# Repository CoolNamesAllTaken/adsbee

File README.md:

# ADSBee

ADSBee is a family of open-source, dual-band ADS-B receivers from [Pants for Birds LLC](https://pantsforbirds.com). Every ADSBee decodes 1090 MHz Mode S / ADS-B and 978 MHz UAT transmissions onboard — no SDR dongle, FPGA, or host computer required — maintains an aircraft dictionary, and streams tracked aircraft over UART (and, on the 1090 family, WiFi / Ethernet) in a wide range of output protocols. This repository holds the firmware, hardware design files, datasheets, and host software for the whole family.

There are two product lines, which share most of their firmware (`firmware/common/`):

| | **ADSBee 1090** | **ADSBee 1421** |
|---|---|---|
| Best for | Ground stations, feeders, networked receivers | Ultra-low-power embedded / UAS detect-and-avoid |
| Processors | RP2040 + ESP32-S3 + CC1312 | TI CC1314R10 + Semtech LR2021 |
| 1090 MHz | Custom RF frontend + RP2040 PIO decoder | LR2021 OOK receiver |
| 978 MHz UAT | CC1312 sub-GHz radio | CC1314 sub-GHz radio (uplink reception selectable) |
| Interfaces | USB, UART, WiFi, Ethernet (PoE pant / W5500), GNSS | UART (AT commands), SYNC line, LR2021 SPI passthrough |
| Power | ~1W | ~19 mA at 1.8–3.3 V |
| Firmware | [`firmware/adsbee_1090/`](firmware/adsbee_1090/) | [`firmware/adsbee_1421/`](firmware/adsbee_1421/) |

## Safety Notice

We work hard to make ADSBee products performant and reliable, but not all aircraft broadcast their location, messages can be lost or corrupted, and hardware or software can fail. ADSBee cannot guarantee detection or accurate reporting of all traffic. Users are responsible for evaluating its suitability for their application and for the safe operation of any system it is integrated into. See our [terms of sale](https://pantsforbirds.com/terms-of-sale/#warranty) and [license](LICENSE) for full terms.

## Products and Where to Buy

All ADSBee devices are designed and sold by Pants for Birds LLC. Purchasing a device is the best way to support the project. Product pages, datasheets, and the [Quick Start Guide](https://pantsforbirds.com/adsbee/quick-start/) live at [pantsforbirds.com](https://pantsforbirds.com/adsbee/).

### ADSBee 1090 family

| | |
|---|---|
|  | **[ADSBee 1090U](https://pantsforbirds.com/product/adsbee-1090u/)** — RP2040, ESP32-S3, CC1312, and a custom 1090 MHz RF frontend on a single PCBA, enabling all multi-band receive and networking functions (Ethernet requires an external pant). [Datasheet](word/exports/datasheet_adsbee_1090.pdf) |
|  | **[ADSBee m1090](https://pantsforbirds.com/product/adsbee-m1090/)** — solder-down module containing only the 1090 MHz frontend and RP2040. Add a CC1312 and ESP32 on your carrier board for the full 1090U feature set, running the same firmware image. Drops one of the 1090U's two LNA stages for lower power and better ultra-close-range performance; populate an external LNA on the carrier for equivalent maximum range. An [m1090 Eval Board](https://pantsforbirds.com/product/adsbee-m1090-eval-board/) is available ([datasheet](word/exports/datasheet_adsbee_m1090_eval_board.pdf)). |
|  | **[GS3M PoE](https://pantsforbirds.com/product/adsbee-gs3m-poe/)** — the ADSBee 1090U in a ruggedized, weatherproof enclosure, connected and powered over 802.3af Power over Ethernet for industrial and outdoor installations. [Datasheet](word/exports/datasheet_gs3m_poe.pdf) |

### ADSBee 1421 family

| | |
|---|---|
|  | **[ADSBee m1421](https://pantsforbirds.com/product/adsbee-m1421/)** — high-performance, ultra-low-power dual-band receiver module (TI CC1314R10 + Semtech LR2021). Receives 1090 MHz Mode S and 978 MHz UAT, tracks up to 400 aircraft onboard, and reports over UART. Weighs 1.85 g. [Datasheet](word/exports/datasheet_adsbee_m1421.pdf) |
|  | **[ADSBee 1421 Developer Kit](https://pantsforbirds.com/product/adsbee-1421-devkit/)** — compact carrier board for the m1421 with a power combiner so a single lightweight dual-band antenna feeds both the 1090 MHz and 978 MHz inputs. Includes the PCBA with ARM-JTAG header, wire harness, USB programmer, and a dual-band ADS-B antenna. [Datasheet](word/exports/datasheet_adsbee_1421_devkit.pdf) |

## ADSBee 1090

ADSBee 1090 is an open-source multi-band radio receiver and decoder for ADS-B packets transmitted by aircraft and ground stations. It is based on an RP2040 microcontroller and utilizes two independent PIO blocks to find and decode ADS-B messages without the need for an FPGA. ADSBee 1090 includes a radio receiver frontend with filtering and amplification, as well as a software-defined comparator circuit with an adjustable trigger threshold for customizable receive sensitivity in a diverse range of RF environments.

### Features
* Decoding of 1090 MHz transponder signals (ADS-B and Mode S).
* Decoding of 978 MHz UAT transponder signals (ADS-B) and uplink data (FIS-B/TIS-B).
* 1x USB console input / output for changing parameters and transmitting data.
* 1x UART for reporting data or ingesting GNSS information.
* Built-in EEPROM for storing nonvolatile settings.
* Feature-rich AT command set for customizing baud rates, output data protocols, signal conditioning values, etc.
* Multiple supported output protocols:
    * Raw packets
    * MAVLINK1
    * MAVLINK2
    * GDL90
    * Mode S Beast
    * Aircraft JSON
    * CSBee (custom information-rich ASCII protocol)
* 2.4 GHz 802.11 radio for automatic streaming of decoded values to custom endpoints on the internet. No external compute required, just add WiFi and power!
* Ethernet interface (requires external PoE pant or W5500 IC).
* GNSS module connector for MLAT and ground station location information.
* ~1W power draw.

### Architecture
ADSBee 1090 utilizes some basic RF hardware (SAW filters, LNA, logarithmic power detector) to amplify the received pulse-position-modulated ADS-B waveform into a pulse train that is conditioned by a comparator and fed to a PIO input pin on the RP2040. The RP2040 utilizes two PIO state machines, one for preamble detection and one for Manchester decoding of the message body, to decode the ADS-B message. This offers significant cost and power savings over FPGA-based solutions that solve the same problem.

A filtered PWM output from the RP2040 can be used to adjust the bias of the data slicer comparator circuit on the output of the receive signal chain, allowing logarithmic adjustments in receiver sensitivity which can be used to filter out weaker ADS-B signals in congested environments or maximize sensitivity for increased receive range.

There are two devices connected to the RP2040 via a common SPI bus: a CC1312 for secondary band receive and an ESP32-S3 for networking functions.

The CC1312 can be tuned to a variety of sub-GHz frequencies to decode UAT messages (and potentially more protocols in the future). These messages are forwarded to the RP2040 over SPI and reported through a unified interface along with the Mode S packets received by the RP2040.

The ESP32-S3 ingests raw packets from the RP2040 and maintains its own aircraft dictionary for reporting over network interfaces (WiFi, Ethernet). The RP2040's dictionary holds 400 aircraft for its USB and UART outputs; the ESP32-S3's holds 200.

All three microcontrollers utilize code stored on the RP2040's external flash chip, so firmware updates are conducted by flashing a single firmware image to the RP2040, which in turn flashes updated firmware images to the CC1312 and ESP32-S3.

## ADSBee 1421

ADSBee 1421 is an ultra-low-power dual band ADS-B receiver, built around a TI CC1314R10 low-power RF MCU and a Semtech LR2021 radio. The LR2021 provides best-in-class sensitivity for the high-baud-rate OOK 1090 MHz Mode S waveform, while the CC1314's sub-GHz RF core receives 978 MHz UAT and its Cortex-M33 does all demodulation, FEC, decoding, and aircraft tracking. The whole receiver draws about 19 mA and weighs under 2 g, making it suited to UAS detect-and-avoid and other power- and weight-constrained applications.

### Features
* Decoding of 1090 MHz transponder signals (ADS-B and Mode S), with selectable preamble modes for range vs. message-type coverage (`AT+R1090_PREAMBLE`).
* Decoding of 978 MHz UAT transponder signals (ADS-B) and ground uplink data (FIS-B/TIS-B). Uplink reception can be disabled independently (`AT+SUBG_MODE=UAT_RX_NO_UPLINK`) to save airtime and CPU when only traffic is needed.
* Onboard aircraft dictionary for up to 400 simultaneous targets.
* UART console with a feature-rich AT command set (baud rate, output protocol, receiver position, gain, logging, …); settings persist in flash.
* Multiple supported output protocols: Raw packets, CSBee, MAVLINK1, MAVLINK2, GDL90, Mode S Beast, Aircraft JSON.
* SYNC line for host-controlled deep sleep (STANDBY with SRAM retained), which also hands the LR2021 SPI bus to an external MCU — e.g. to use the LR2021's 2.4 GHz radio for LoRa or mesh networking.
* Firmware updates over the UART ROM bootloader (no debugger needed) or JTAG. Holding SYNC high through a reset enters the bootloader, so any host that drives a USB-UART adapter's RTS → SYNC and DTR → RESET_N (or the included ADSBee 1421 Programmer) can reflash the module remotely. See [Reflashing over UART: the SYNC bootloader backdoor](firmware/adsbee_1421/README.md#reflashing-over-uart-the-sync-bootloader-backdoor).
* Ultra-low power: ~19 mA at 1.8–3.3 V.

### Architecture
The CC1314R10 runs a NoRTOS super-loop: it polls the LR2021 over SPI for 1090 MHz OOK frames, services its own RF core's UAT receptions (ADS-B and uplink are distinguished by sync word, so uplink can be switched off at the radio), runs the shared Mode S / UAT decoders and aircraft dictionary from `firmware/common/`, and reports over the console UART. A host can suspend the device by driving SYNC high; on wake the receiver re-initializes itself. SYNC is also the ROM bootloader backdoor pin, so a reset while SYNC is high enters the serial bootloader. See [`firmware/adsbee_1421/AGENTS.md`](firmware/adsbee_1421/AGENTS.md) for the build guide and the SYNC sleep / LR2021 bus-handoff contract, and the [m1421 datasheet](word/exports/datasheet_adsbee_m1421.pdf) for the full AT command reference.

## Repository Layout

| Path | Contents |
|---|---|
| [`firmware/`](firmware/) | All firmware. [`adsbee_1090/`](firmware/adsbee_1090/) (RP2040 `pico/`, `esp/`, CC1312 `ti/`), [`adsbee_1421/`](firmware/adsbee_1421/) (CC1314 `ti/`, RP2040-Zero `programmer/`, the ADSBee 1421 Programmer), [`common/`](firmware/common/) (shared decoders, aircraft dictionary, comms, settings), `modules/` (submodules: cppAT, googletest, …), [`scripts/`](firmware/scripts/) (dev tooling), [`build.sh`](firmware/build.sh) dispatcher. |
| [`software/`](software/) | Host software: [`adsbee_1421_console/`](software/adsbee_1421_console/) (single-file Web Serial console + UART flasher for the 1421), `adsbee/` (Python package), `serial_logger/`, and `tar1090/` / `ultrafeeder/` / `ultra2/` feeder compose files. |
| [`ci/`](ci/) | Hardware-in-the-loop USB/UF2 + OTA flash test run by the self-hosted CI runner. |
| [`kicad/`](kicad/) | Hardware design files (ADSBee 1090, 1090U, frontend prototypes, panels). |
| [`3d/`](3d/) | Enclosure exports and CAD links. |
| [`ltspice/`](ltspice/), [`excel/`](excel/) | RF / analog simulations and design calculations. |
| [`affinity/`](affinity/) | Diagrams and promotional artwork sources. |
| [`word/`](word/) | Product datasheets and firmware reference guide (`.docx` sources, PDFs in [`word/exports/`](word/exports/)). |
| [`references/`](references/) | Protocol specifications and component datasheets. |
| [`images/`](images/) | Images used by this README. |

## Building and Flashing Firmware

All toolchains live in Docker containers, so the only host requirements are Docker and git.

```bash
git clone https://github.com/CoolNamesAllTaken/adsbee.git
cd adsbee
bash firmware/scripts/setup_dev.sh        # init submodules + install the pre-commit version-check hook
bash firmware/build.sh adsbee_1090        # RP2040 + ESP32-S3 + CC1312 -> combined.uf2
bash firmware/build.sh adsbee_1421        # CC1314R10 -> adsbee_1421-<version>.hex
```

* **[`firmware/README.md`](firmware/README.md)** — prerequisites, the build dispatcher, build targets and outputs.
* **[`firmware/AGENTS.md`](firmware/AGENTS.md)** — firmware architecture overview and the version-management rules.
* **ADSBee 1090:** [`firmware/adsbee_1090/Developers_Guide.md`](firmware/adsbee_1090/Developers_Guide.md) covers the three-processor build order, flashing (`combined.uf2` over USB BOOTSEL, or OTA through the ESP32 web interface), and recovery.
* **ADSBee 1421:** [`firmware/adsbee_1421/AGENTS.md`](firmware/adsbee_1421/AGENTS.md) covers the build; flash over JTAG with a J-Link ([`firmware/adsbee_1421/ti/README.md`](firmware/adsbee_1421/ti/README.md)), or over UART using the ROM bootloader ([SYNC bootloader backdoor](firmware/adsbee_1421/README.md#reflashing-over-uart-the-sync-bootloader-backdoor)) via the [ADSBee 1421 Programmer](firmware/adsbee_1421/programmer/README.md) (an RP2040-Zero board included in the Developer Kit), a host script driving RTS/DTR, or the **Upload Firmware** button in the [web console](software/adsbee_1421_console/README.md).

Prebuilt firmware is published on the [Releases page](https://github.com/CoolNamesAllTaken/adsbee/releases). Releases are tagged per product as `adsbee_1090-<major>.<minor>.<patch>` and `adsbee_1421-<major>.<minor>.<patch>` (release candidates carry an `-rcN` suffix). `AT+DEVICE_INFO?` reports the firmware version running on a device.

## Support, Bugs, and Feature Requests

* **Getting started / using a device:** start with the [Quick Start Guide](https://pantsforbirds.com/adsbee/quick-start/) and the product datasheets in [`word/exports/`](word/exports/) (AT command reference, reporting protocols, pinouts).
* **Purchasing, orders, warranty, and hardware support:** contact Pants for Birds through [pantsforbirds.com/contact](https://pantsforbirds.com/contact/).
* **Firmware / software bugs:** open a [GitHub Issue](https://github.com/CoolNamesAllTaken/adsbee/issues). Please include:
  * which product (1090U, m1090, GS3M PoE, m1421, 1421 Developer Kit) and the output of `AT+DEVICE_INFO?` (part code and firmware version);
  * what you expected vs. what happened, and steps to reproduce;
  * relevant console output (`AT+LOG_LEVEL=INFO` makes the device chattier) and, for the 1090 family, the web interface/feed configuration involved.
* **Feature requests and questions:** also welcome as GitHub Issues; please tag the title with the product family.

## Contributing

Contributions are welcome (bug fixes, new output protocols, decoder improvements, documentation, etc)! Please follow the steps below to contribute a change.

1. Fork the repo and create a branch from `main`.
2. Run `bash firmware/scripts/setup_dev.sh` once. It initializes submodules and installs a git pre-commit hook that enforces the version rule below.
3. Make your change. Any change under `firmware/adsbee_1090/`, `firmware/adsbee_1421/`, or `firmware/common/` must ship under a firmware version that has not been released yet for the affected product(s) (`firmware/common/coprocessor/object_dictionary.cpp` for 1090, `firmware/adsbee_1421/ti/object_dictionary/object_dictionary.cpp` for 1421; a `common/` change concerns both). If main is already on the next unreleased RC, keep it; if its version matches a release tag, move to the next unreleased RC. Note that devices only reflash coprocessors on a version mismatch, so you will need to force a reflash or bump the software version to test your code [`firmware/AGENTS.md`](firmware/AGENTS.md). When have finished testing and go to you submit your PR, ensure that your firmware version matches the version string in main! Firmware versions are only rolled upon each release.
4. If you add or change an AT command, reporting protocol, or other user-visible behavior, update the corresponding datasheet in [`word/`](word/).
5. Build locally with `firmware/build.sh` and, for 1090 changes, run the host unit tests (`bash firmware/build.sh adsbee_1090 test`).
6. Open a pull request against `main`. [CI](https://github.com/CoolNamesAllTaken/adsbee/actions/workflows/firmware.yml) builds every target and runs the unit tests; the hardware-in-the-loop flash test runs on `main` after merge.

By contributing you agree that your contributions are licensed under the GPL-3.0.

## License

ADSBee firmware, software, and design files in this repository are released under the [GNU General Public License v3.0](LICENSE). ADSBee is a product of Pants for Birds LLC.

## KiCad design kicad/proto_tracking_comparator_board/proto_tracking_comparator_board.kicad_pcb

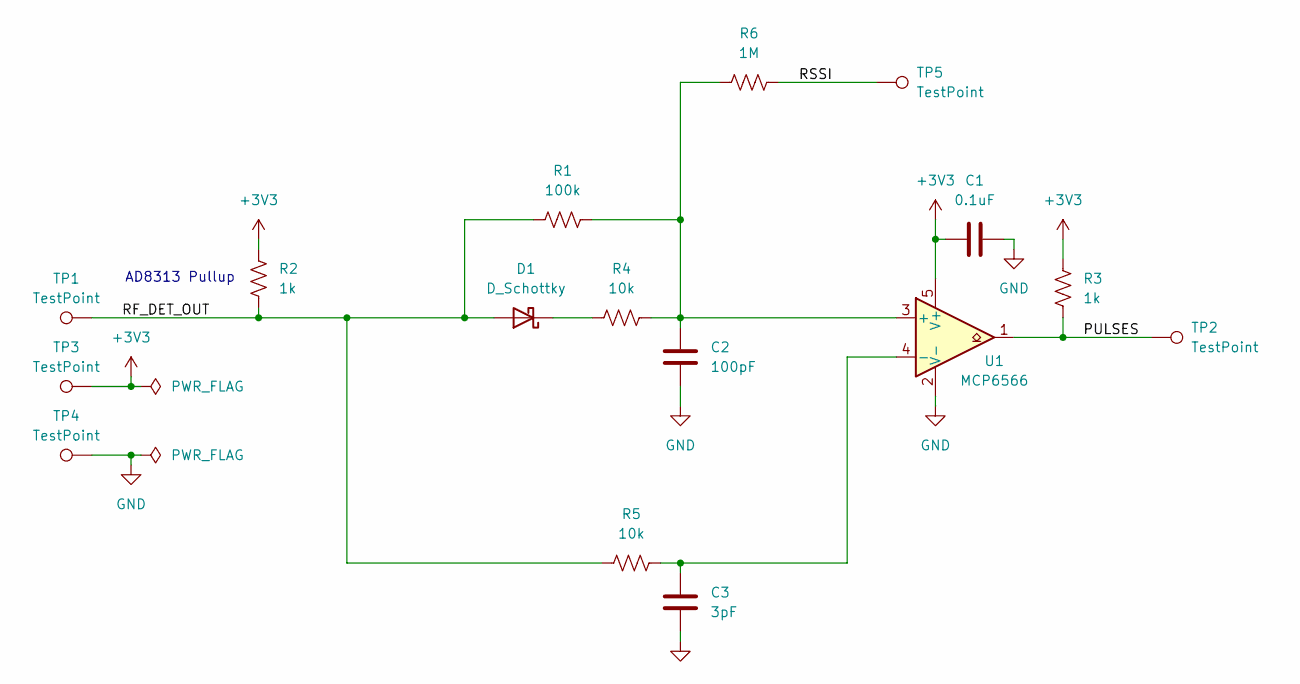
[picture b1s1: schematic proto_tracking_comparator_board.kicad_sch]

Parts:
C1: 0.1uF; C_0603_1608Metric
C2: 100pF; C_0603_1608Metric
C3: 3pF; C_0603_1608Metric
D1: D_Schottky; D_0402_1005Metric
R1: 100k; R_0603_1608Metric
R2, R3: 1k; R_0603_1608Metric
R4, R5: 10k; R_0603_1608Metric
R6: 1M; R_0603_1608Metric
TP1, TP2, TP3, TP4, TP5: TestPoint; TestPoint_Pad_1.0x1.0mm
U1: MCP6566; SOT-353_SC-70-5

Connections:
+3V3: C1.2, R2.1, R3.1, TP3.1, U1.5 (V+)
/PULSES: R3.2, TP2.1, U1.1
/RF_DET_OUT: D1.2 (A), R1.1, R2.2, R5.1, TP1.1
/RSSI: R6.2, TP5.1
GND: C1.1, C2.2, C3.2, TP4.1, U1.2 (V-)
unnamed: D1.1 (K), R4.1
unnamed: C2.1, R1.2, R4.2, R6.1, U1.3 (+)
unnamed: C3.1, R5.2, U1.4 (-)

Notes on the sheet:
AD8313 Pullup

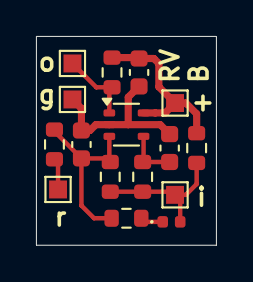
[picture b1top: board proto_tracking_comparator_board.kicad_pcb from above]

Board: 2 copper layers, 10.0 x 11.6 mm, 16 parts (0 on the bottom side), 8 nets.

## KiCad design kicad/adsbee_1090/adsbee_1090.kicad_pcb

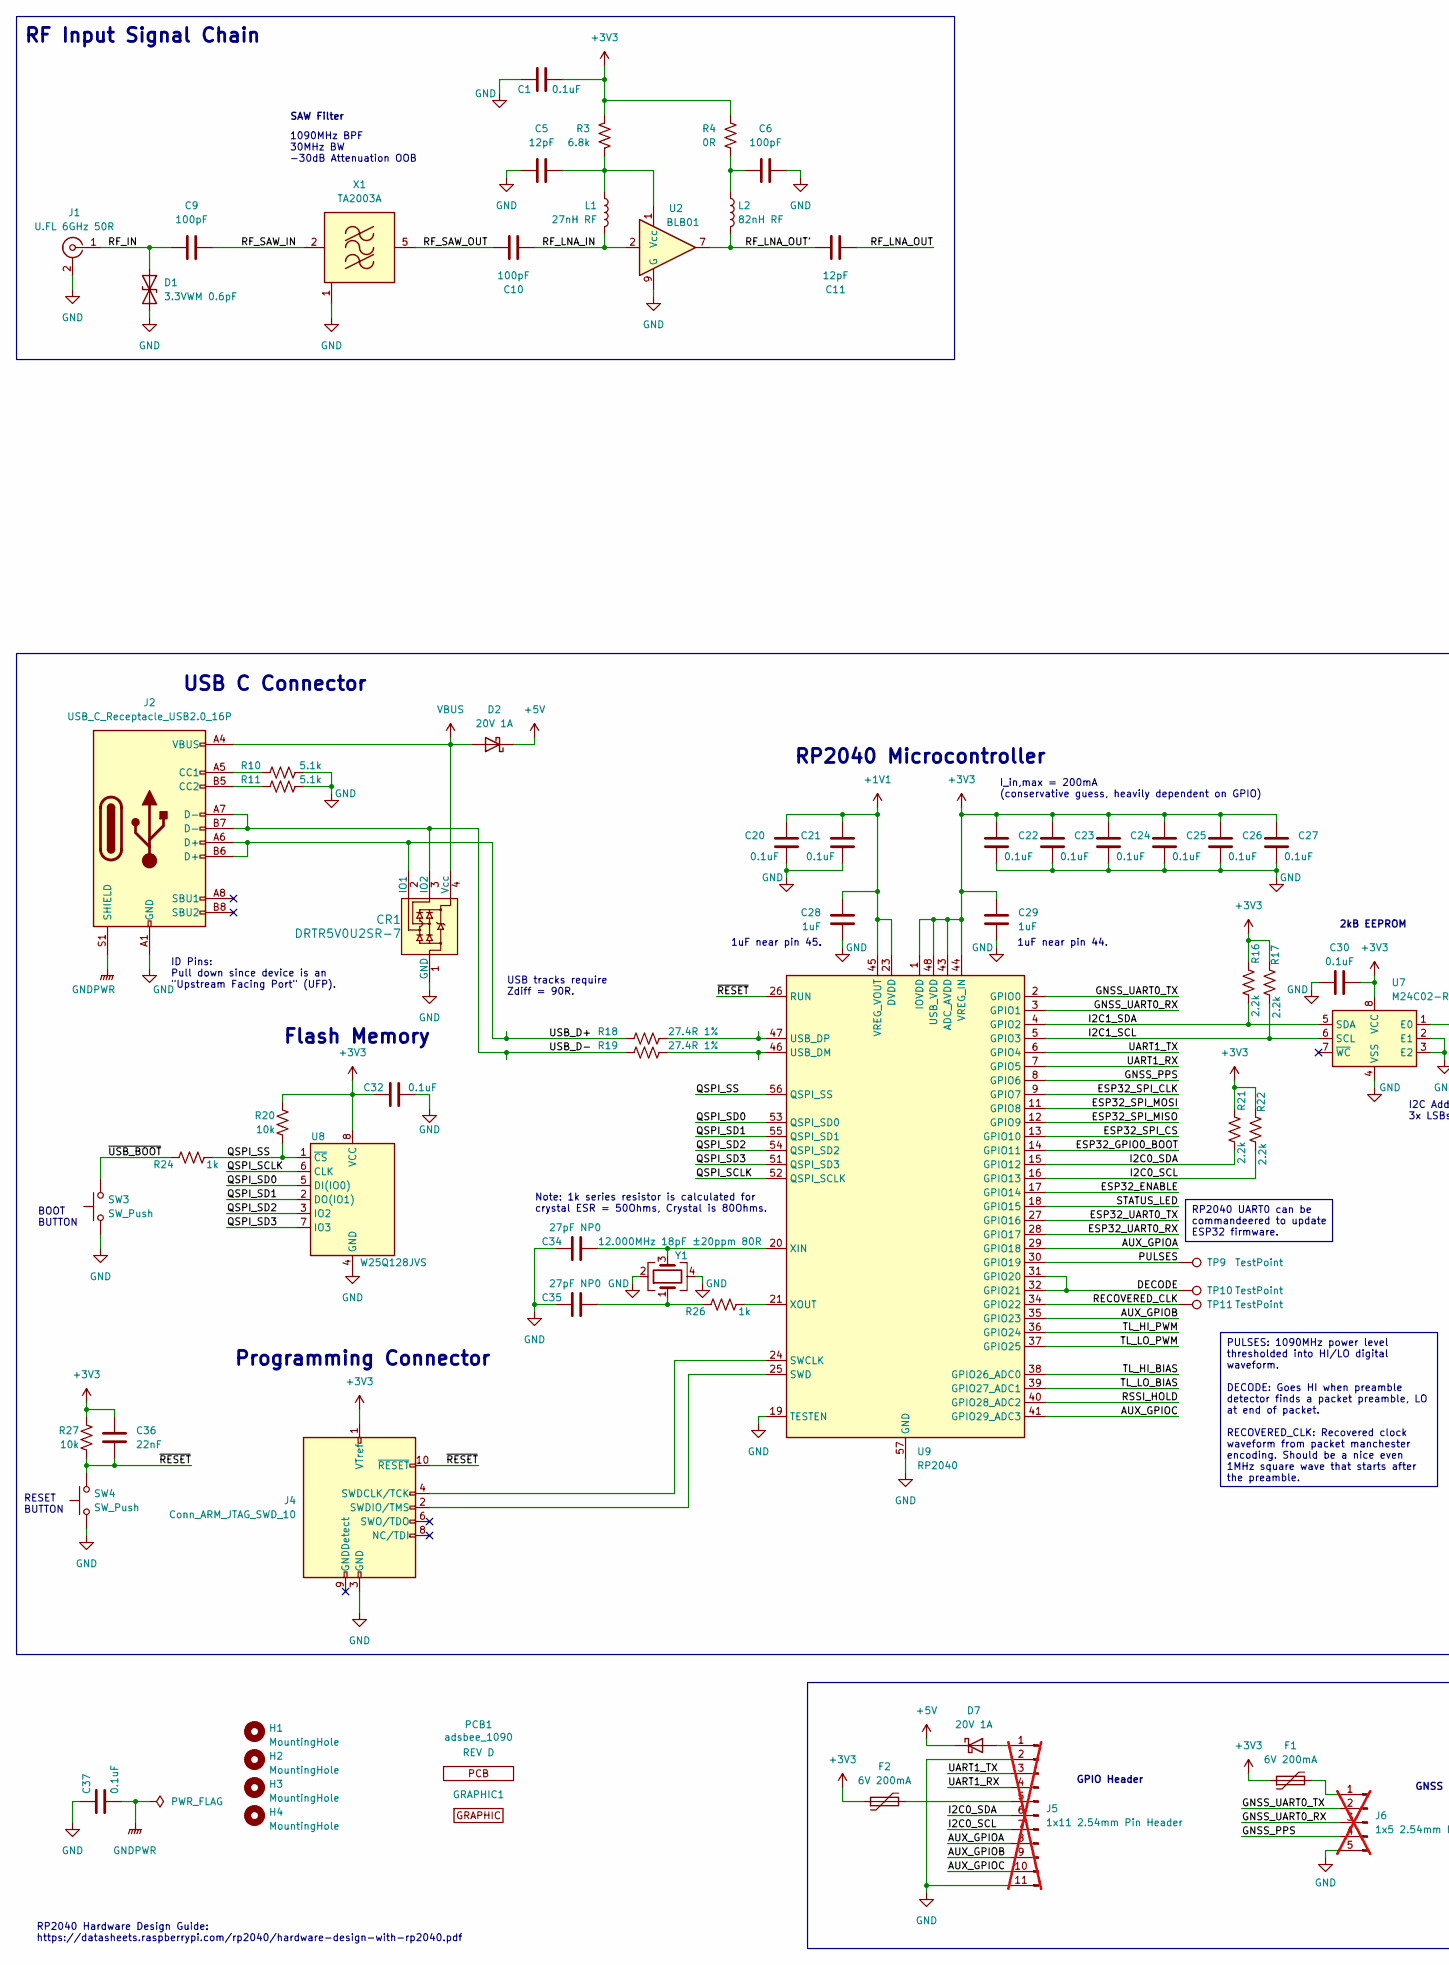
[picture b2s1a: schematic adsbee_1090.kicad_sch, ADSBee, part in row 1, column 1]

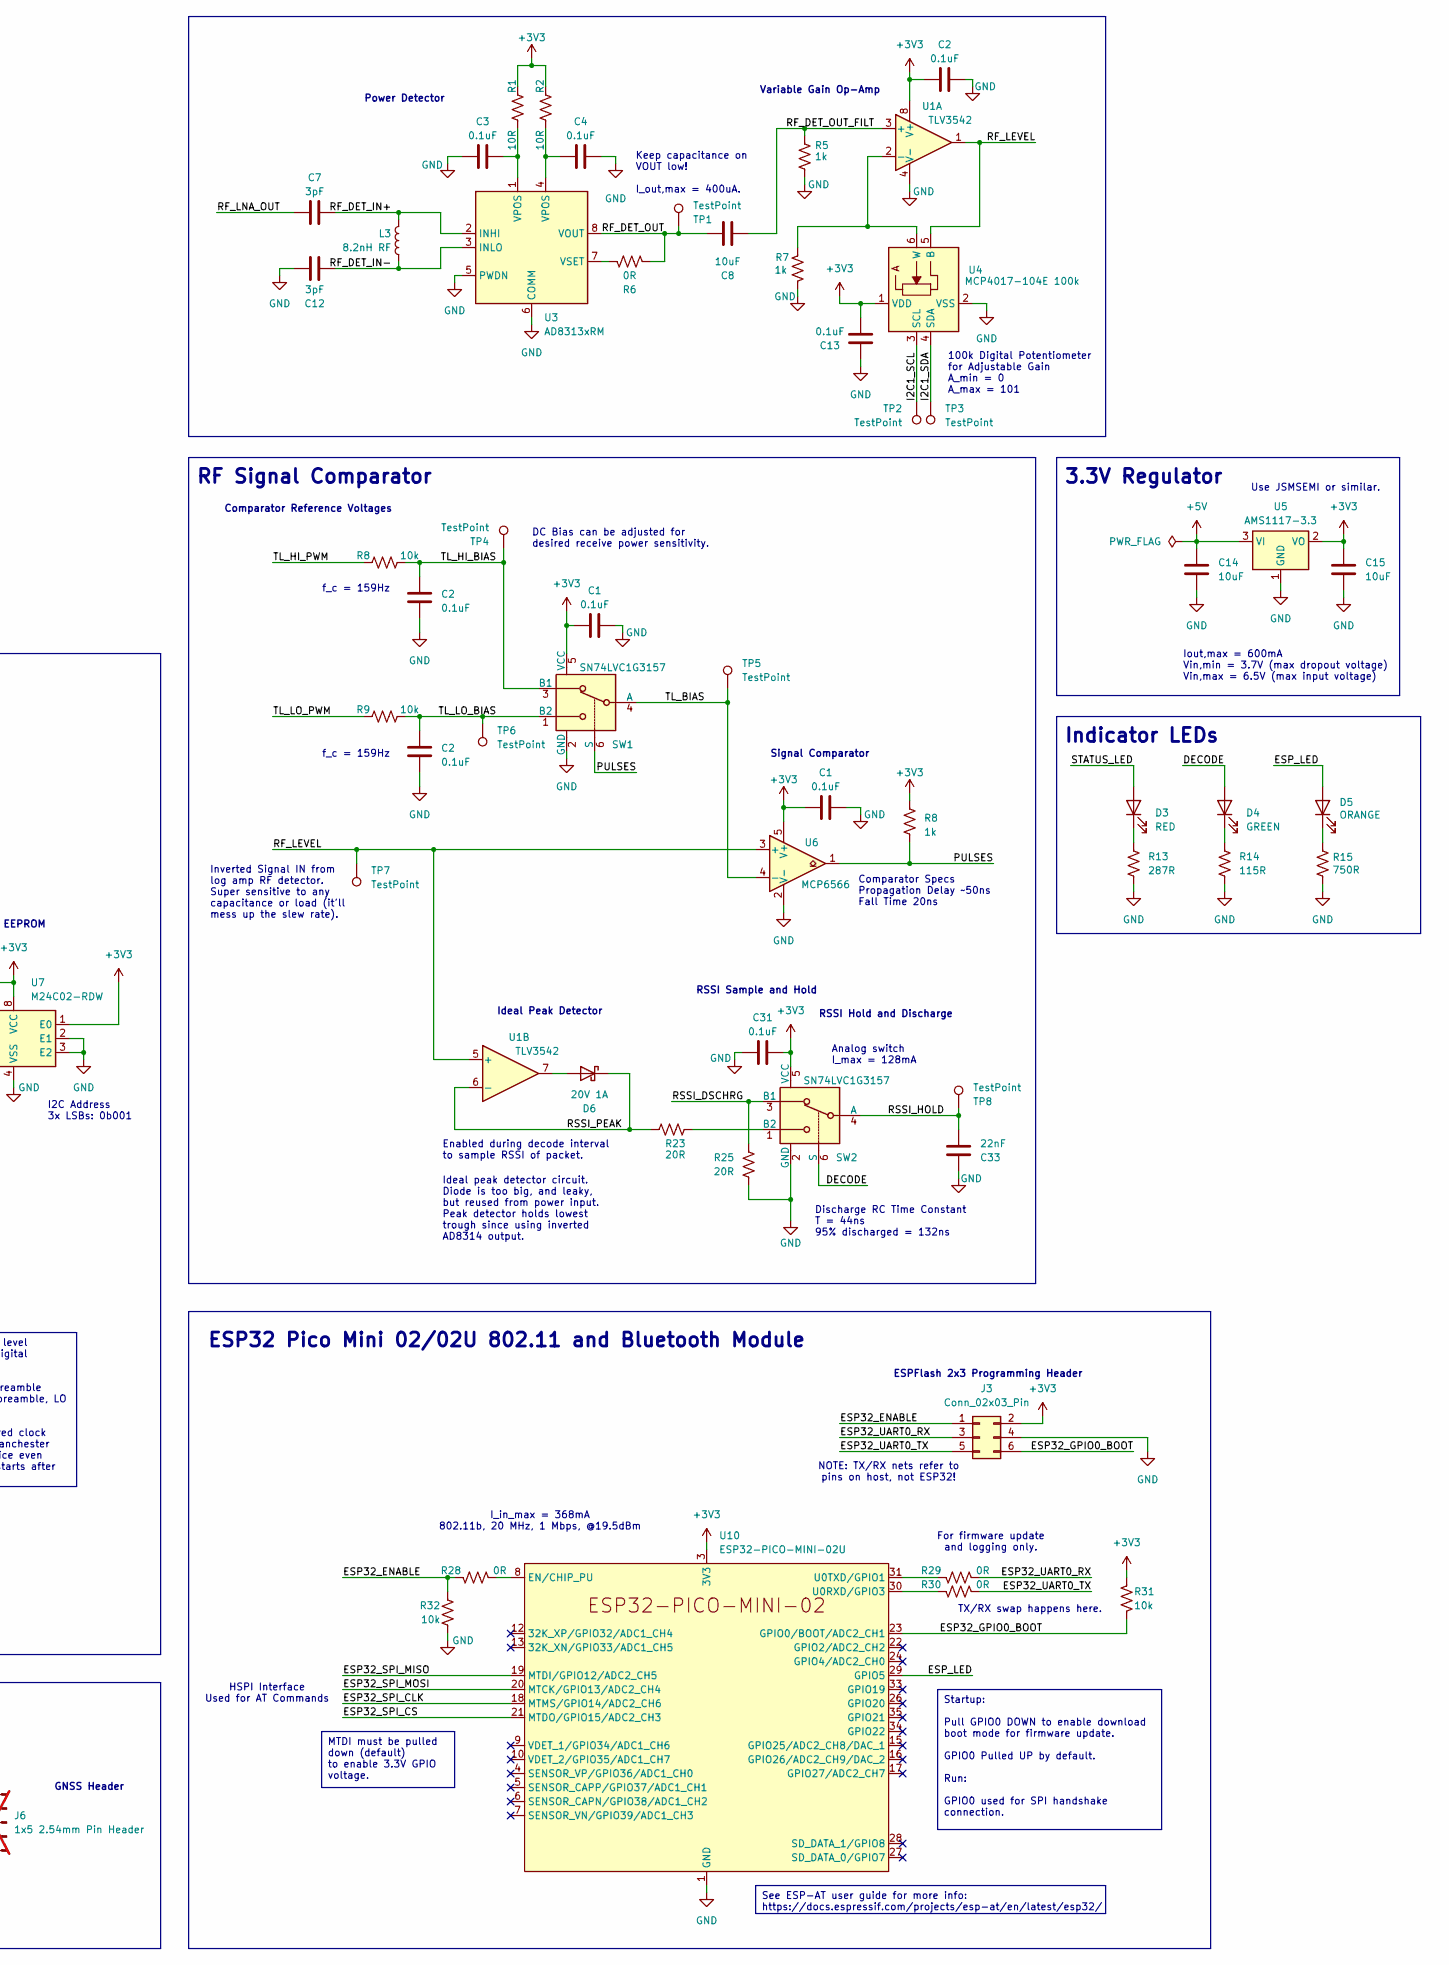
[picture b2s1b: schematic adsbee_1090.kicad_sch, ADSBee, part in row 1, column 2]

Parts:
C1, C2, C3, C4, C13, C20, C21, C22, C23, C24, C25, C26, C27, C30, C31, C32, C37: 0.1uF; C_0402_1005Metric; MPN C60474
C5, C11: 12pF; C_0402_1005Metric; MPN C326662
C6, C9, C10: 100pF; C_0402_1005Metric; MPN C106200
C7, C12: 3pF; C_0402_1005Metric; MPN C1855211
C8, C14, C15: 10uF; C_0805_2012Metric; MPN C95841
C28, C29: 1uF; C_0603_1608Metric; MPN C29936
C33, C36: 22nF; C_0402_1005Metric; MPN C107026
C34, C35: 27pF NP0; C_0402_1005Metric; MPN C107002
CR1: DRTR5V0U2SR-7; SOT-143; MPN C443828
D1: 3.3VWM 0.6pF; D_SOD-523; MPN C2912559
D2, D6, D7: 20V 1A; D_SOD-123; MPN C82288
D3: RED; LED_0603_1608Metric; MPN C510027
D4: GREEN; LED_0603_1608Metric; MPN C510025
D5: ORANGE; LED_0603_1608Metric; MPN C510024
F1, F2: 6V 200mA; Fuse_0402_1005Metric; MPN C914085
GRAPHIC1: Graphic; ADSBee
H1, H2, H3, H4: MountingHole; MountingHole_2.7mm_M2.5_Isolated
J1: U.FL 6GHz 50R; Hirose_U.FL-R-SMT-1; MPN C88374
J2: USB_C_Receptacle_USB2.0_16P; USB_C_Receptacle_GCT_USB4105-xx-A_16P_TopMnt_Horizontal; MPN C2765186
J3: Conn_02x03_Pin; PinHeader_2x03_P1.27mm_Vertical_SMD; MPN C3975186
J4: Conn_ARM_JTAG_SWD_10; PinHeader_2x05_P1.27mm_Vertical_SMD; MPN C2935458
J5: 1x11 2.54mm Pin Header; PinHeader_1x11_P2.54mm_Vertical; MPN C2894934; not fitted
J6: 1x5 2.54mm Pin Header; PinHeader_1x05_P2.54mm_Vertical; MPN C492404; not fitted
L1: 27nH RF; L_0402_1005Metric; MPN C408697
L2: 82nH RF; L_0402_1005Metric; MPN C54972
L3: 8.2nH RF; L_0402_1005Metric; MPN C361505
PCB1: PCB; PCB_PN_REV_Small; MPN adsbee_1090
R1, R2: 10R; R_0402_1005Metric; MPN C138066
R3: 6.8k; R_0402_1005Metric; MPN C93940
R4, R6, R28, R29, R30: 0R; R_0402_1005Metric; MPN C60485
R5, R7, R24, R26: 1k; R_0402_1005Metric; MPN C106235
R8, R9, R20, R27, R31, R32: 10k; R_0402_1005Metric; MPN C60490
R10, R11: 5.1k; R_0402_1005Metric; MPN C105872
R13: 287R; R_0402_1005Metric; MPN C375493
R14: 115R; R_0402_1005Metric; MPN C295872
R15: 750R; R_0402_1005Metric; MPN C137936
R16, R17, R21, R22: 2.2k; R_0402_1005Metric; MPN C114762
R18, R19: 27.4R 1%; R_0402_1005Metric; MPN C284479
R23, R25: 20R; R_0402_1005Metric; MPN C138031
SW1, SW2: SN74LVC1G3157; SOT-363_SC-70-6; MPN C38663
SW3, SW4: SW_Push; SW-SMD_L3.9-W3.0-P4.45; MPN C455280
TP1, TP2, TP3, TP4, TP5, TP6, TP7, TP8, TP9, TP10, TP11: TestPoint; TestPoint_Pad_D1.0mm
U1: TLV3542; VSSOP-8_3.0x3.0mm_P0.65mm; MPN C2876465
U2: BLB01; DFN-8-1EP_2x2mm_P0.5mm_EP0.9x1.5mm
U3: AD8313xRM; MSOP-8_3x3mm_P0.65mm; MPN C481897
U4: MCP4017-104E 100k; SOT-363_SC-70-6; MPN C510890
U5: AMS1117-3.3; SOT-223-3_TabPin2; MPN C917183
U6: MCP6566; SOT-353_SC-70-5; MPN C623508
U7: M24C02-RDW; TSSOP-8_4.4x3mm_P0.65mm; MPN C152731
U8: W25Q128JVS; SOIC-8_5.23x5.23mm_P1.27mm; MPN C97521
U9: RP2040; QFN-56-1EP_7x7mm_P0.4mm_EP3.2x3.2mm; MPN C2040
U10: ESP32-PICO-MINI-02U; MPN C3013939
X1: TA2003A; Filter_SAW-6_3.0x3.0mm
Y1: 12.000MHz 18pF ±20ppm 80R; Crystal_SMD_3225-4Pin_3.2x2.5mm; MPN C403945

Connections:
+1V1: C20.2, C21.2, C28.2, U9.23 (DVDD), U9.45 (VREG_VOUT), U9.50 (DVDD)
+5V: C14.1, D2.1 (K), D7.1 (K), U5.3 (VI)
/AUX_GPIOA: J5.8, U9.29 (GPIO18)
/AUX_GPIOB: J5.9, U9.35 (GPIO23)
/AUX_GPIOC: J5.10, U9.41 (GPIO29_ADC3)
/DECODE: D4.2 (A), SW2.6 (S), TP10.1, U9.31 (GPIO20), U9.32 (GPIO21)
/ESP32_ENABLE: J3.1, R28.1, R32.1, U9.17 (GPIO14)
/ESP32_GPIO0_BOOT: J3.6, R31.2, U9.14 (GPIO11), U10.23 (GPIO0/BOOT/ADC2_CH1)
/ESP32_SPI_CLK: U9.9 (GPIO7), U10.18 (MTMS/GPIO14/ADC2_CH6)
/ESP32_SPI_CS: U9.13 (GPIO10), U10.21 (MTDO/GPIO15/ADC2_CH3)
/ESP32_SPI_MISO: U9.12 (GPIO9), U10.19 (MTDI/GPIO12/ADC2_CH5)
/ESP32_SPI_MOSI: U9.11 (GPIO8), U10.20 (MTCK/GPIO13/ADC2_CH4)
/ESP32_UART0_RX: J3.3, R29.2, U9.28 (GPIO17)
/ESP32_UART0_TX: J3.5, R30.2, U9.27 (GPIO16)
/ESP_LED: D5.2 (A), U10.29 (GPIO5)
/GNSS_PPS: J6.4, U9.8 (GPIO6)
/GNSS_UART0_RX: J6.3, U9.3 (GPIO1)
/GNSS_UART0_TX: J6.2, U9.2 (GPIO0)
/I2C0_SCL: J5.7, R22.2, U9.16 (GPIO13)
/I2C0_SDA: J5.6, R21.2, U9.15 (GPIO12)
/I2C1_SCL: R17.2, TP2.1, U4.3 (SCL), U7.6 (SCL), U9.5 (GPIO3)
/I2C1_SDA: R16.2, TP3.1, U4.4 (SDA), U7.5 (SDA), U9.4 (GPIO2)
/QSPI_SCLK: U8.6 (CLK), U9.52 (QSPI_SCLK)
/QSPI_SD0: U8.5 (DI(IO0)), U9.53 (QSPI_SD0)
/QSPI_SD1: U8.2 (DO(IO1)), U9.55 (QSPI_SD1)
/QSPI_SD2: U8.3 (IO2), U9.54 (QSPI_SD2)
/QSPI_SD3: U8.7 (IO3), U9.51 (QSPI_SD3)
/QSPI_SS: R20.2, R24.2, U8.1 (~CS), U9.56 (QSPI_SS)
/RECOVERED_CLK: TP11.1, U9.34 (GPIO22)
/RF_DET_IN+: C7.2, L3.1, U3.2 (INHI)
/RF_DET_IN-: C12.2, L3.2, U3.3 (INLO)
/RF_DET_OUT: C8.1, R6.2, TP1.1, U3.8 (VOUT)
/RF_DET_OUT_FILT: C8.2, R5.1, U1.3 (+)
/RF_IN: C9.1, D1.1 (A1), J1.1 (In)
/RF_LEVEL: TP7.1, U1.1, U1.5 (+), U4.5 (B), U6.3 (+)
/RF_LNA_OUT: C7.1, C11.2
/RF_LNA_OUT': C11.1, L2.2, U2.7
/RF_SAW_IN: C9.2, X1.2 (IN)
/RF_SAW_OUT: C10.1, X1.5 (OUT)
/RSSI_DSCHRG: R25.1, SW2.3 (B1)
/RSSI_HOLD: C33.2, SW2.4 (A), TP8.1, U9.40 (GPIO28_ADC2)
/RSSI_PEAK: D6.1 (K), R23.1, U1.6 (-)
/STATUS_LED: D3.2 (A), U9.18 (GPIO15)
/TL_BIAS: SW1.4 (A), TP5.1, U6.4 (-)
/TL_LO_PWM: R9.2, U9.37 (GPIO25)
/UART1_RX: J5.4, U9.7 (GPIO5)
/UART1_TX: J5.3, U9.6 (GPIO4)
/USB_D+: CR1.2 (IO1), J2.A6 (D+), J2.B6 (D+), R18.1
/USB_D-: CR1.3 (IO2), J2.A7 (D-), J2.B7 (D-), R19.1
/~RESET: C36.1, J4.10 (~RESET), R27.2, SW4.2, U9.26 (RUN)
/~USB_BOOT: R24.1, SW3.2
GND: C1.2, C2.2, C3.1, C4.2, C5.1, C6.2, C12.1, C13.1, C14.2, C15.2, C20.1, C21.1, C22.1, C23.1, C24.1, C25.1, C26.1, C27.1, C28.1, C29.1, C30.1, C31.1, C32.2, C33.1, C34.1, C35.1, C37.2, CR1.1 (GND), D1.2 (A2), J1.2 (Ext), J2.A1 (GND), J2.A12 (GND), J2.B1 (GND), J2.B12 (GND), J3.4, J4.3 (GND), J4.5 (GND), J5.2, J5.11, J6.5, R5.2, R7.2, R10.2, R11.2, R13.2, R14.2, R15.2, R25.2, R32.2, SW1.2 (GND), SW2.2 (GND), SW3.1, SW4.1, U1.4 (V-), U2.9 (G), U3.5 (PWDN), U3.6 (COMM), U4.2 (VSS), U5.1 (GND), U6.2 (V-), U7.2 (E1), U7.3 (E2), U7.4 (VSS), U8.4 (GND), U9.19 (TESTEN), U9.57 (GND), U10.1 (GND), U10.2 (GND), U10.11 (GND), U10.14 (GND), U10.36 (GND), U10.37 (GND), U10.38 (GND), U10.39 (GND), U10.40 (GND), U10.41 (GND), U10.42 (GND), U10.43 (GND), U10.44 (GND), U10.45 (GND), U10.46 (GND), U10.47 (GND), U10.48 (GND), U10.49 (GND), U10.50 (GND), U10.51 (GND), U10.52 (GND), U10.53 (GND), X1.1 (GND), X1.3 (GND), X1.4 (GND), X1.6 (GND), Y1.2, Y1.4; also elsewhere on the board
GNDPWR: C37.1, J2.S1 (SHIELD)
unnamed: C3.2, R1.2, U3.1 (VPOS)
unnamed: C4.1, R2.2, U3.4 (VPOS)
unnamed: C6.1, L2.1, R4.2
unnamed: C10.2, L1.2, U2.2
unnamed: C35.2, R26.1, Y1.1
unnamed: D3.1 (K), R13.1
unnamed: D4.1 (K), R14.1
unnamed: D5.1 (K), R15.1
unnamed: D6.2 (A), U1.7
unnamed: D7.2 (A), J5.1
unnamed: J2.A5 (CC1), R10.1
unnamed: J2.B5 (CC2), R11.1
unnamed: J4.4 (SWDCLK/TCK), U9.24 (SWCLK)
unnamed: J4.2 (SWDIO/TMS), U9.25 (SWD)
unnamed: F2.2, J5.5
unnamed: F1.2, J6.1
unnamed: R23.2, SW2.1 (B2)
unnamed: R7.1, U1.2 (-), U4.6 (W)
unnamed: C5.2, L1.1, R3.2, U2.1 (Vcc)
unnamed: R6.1, U3.7 (VSET)
unnamed: R19.2, U9.46 (USB_DM)
unnamed: R18.2, U9.47 (USB_DP)
unnamed: C34.2, U9.20 (XIN), Y1.3
unnamed: R26.2, U9.21 (XOUT)
unnamed: R28.2, U10.8 (EN/CHIP_PU)
unnamed: R30.1, U10.30 (U0RXD/GPIO3)
unnamed: R29.1, U10.31 (U0TXD/GPIO1)
VBUS: CR1.4 (Vcc), D2.2 (A), J2.A4 (VBUS), J2.A9 (VBUS), J2.B4 (VBUS), J2.B9 (VBUS)

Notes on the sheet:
Startup: Pull GPIO0 DOWN to enable download boot mode for firmware update. GPIO0 Pulled UP by default. Run: GPIO0 used for SPI handshake connection.
PULSES: 1090MHz power level thresholded into HI/LO digital waveform. DECODE: Goes HI when preamble detector finds a packet preamble, LO at end of packet. RECOVERED_CLK: Recovered clock waveform from packet manchester encoding. Should be a nice even 1MHz square wave that starts after the preamble.
MTDI must be pulled down (default) to enable 3.3V GPIO voltage.
See ESP-AT user guide for more info: https://docs.espressif.com/projects/esp-at/en/latest/esp32/
RP2040 UART0 can be commandeered to update ESP32 firmware.
NOTE: TX/RX nets refer to pins on host, not ESP32!
1uF near pin 44.
ESP32 Pico Mini 02/02U 802.11 and Bluetooth Module
Programming Connector
Note: 1k series resistor is calculated for crystal ESR = 50Ohms, Crystal is 80Ohms.
Comparator Reference Voltages
ESPFlash 2x3 Programming Header
Indicator LEDs
1090MHz BPF 30MHz BW -30dB Attenuation OOB
Variable Gain Op-Amp
Keep capacitance on VOUT low! I_out,max = 400uA.
RP2040 Hardware Design Guide: https://datasheets.raspberrypi.com/rp2040/hardware-design-with-rp2040.pdf
100k Digital Potentiometer for Adjustable Gain A_min = 0 A_max = 101
Ideal Peak Detector
f_c = 159Hz
Analog switch I_max = 128mA
I_in,max = 200mA (conservative guess, heavily dependent on GPIO)
Enabled during decode interval to sample RSSI of packet.
GNSS Header
RF Signal Comparator
SAW Filter
Iout,max = 600mA Vin,min = 3.7V (max dropout voltage) Vin,max = 6.5V (max input voltage)
3.3V Regulator
ID Pins: Pull down since device is an "Upstream Facing Port" (UFP).
I2C Address 3x LSBs: 0b001
RF Input Signal Chain
Flash Memory
Signal Comparator
TX/RX swap happens here.
RESET BUTTON
RP2040 Microcontroller
f_c = 159Hz
BOOT BUTTON
Comparator Specs Propagation Delay ~50ns Fall Time 20ns
GPIO Header

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
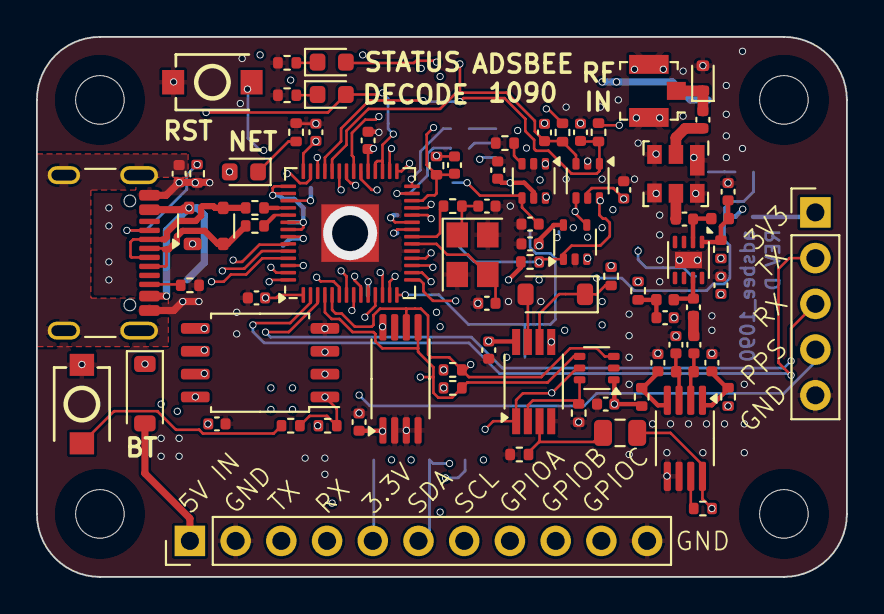
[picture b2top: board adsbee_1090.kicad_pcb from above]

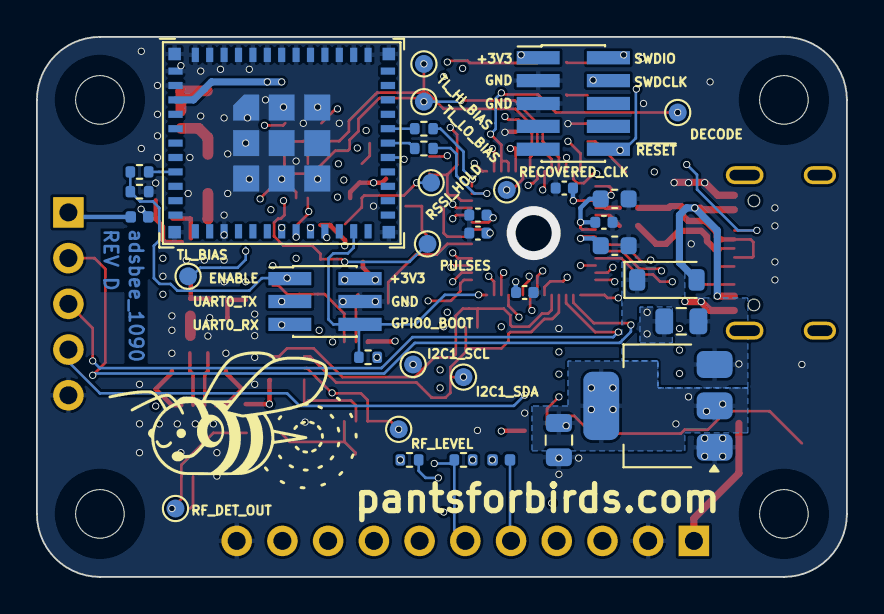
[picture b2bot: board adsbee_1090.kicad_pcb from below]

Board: 6 copper layers, 45.0 x 30.0 mm, 121 parts (36 on the bottom side), 86 nets.

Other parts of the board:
C16, C17, C18, C19: 0.1uF; C_0402_1005Metric
R12: 1k; R_0402_1005Metric

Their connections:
GND: C16.2, C17.2, C18.2, C19.2; also elsewhere on the board

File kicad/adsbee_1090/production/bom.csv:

Designator,Footprint,Quantity,Value,LCSC Part #
"C1, C13, C16, C17, C18, C19, C2, C20, C21, C22, C23, C24, C25, C26, C27, C3, C30, C31, C32, C37, C4",0402,21,0.1uF,C60474
"C10, C6, C9",0402,3,100pF,C106200
"C11, C5",0402,2,12pF,C326662
"C12, C7",0402,2,3pF,C1855211
"C14, C15, C8",0805,3,10uF, C95841
"C28, C29",0603,2,1uF,C29936
"C33, C36",0402,2,22nF,C107026
"C34, C35",0402,2,27pF NP0,C107002
CR1,SOT-143,1,DRTR5V0U2SR-7,C443828
D1,D_SOD-523,1,3.3VWM 0.6pF,C2912559
"D2, D6, D7",D_SOD-123,3,20V 1A,C82288
D3,0603,1,RED,C510027
D4,0603,1,GREEN,C510025
D5,0603,1,ORANGE,C510024
"F1, F2",0402,2,6V 200mA,C914085
J1,Hirose_U.FL-R-SMT-1,1,U.FL 6GHz 50R,C88374
J2,USB_C_Receptacle_GCT_USB4105-xx-A_16P_TopMnt_Horizontal,1,USB_C_Receptacle_USB2.0_16P,C2765186
J3,PinHeader_2x03_P1.27mm_Vertical_SMD,1,Conn_02x03_Pin, C3975186
J4,PinHeader_2x05_P1.27mm_Vertical_SMD,1,Conn_ARM_JTAG_SWD_10, C2935458
L1,0402,1,27nH RF,C408697
L2,0402,1,82nH RF,C54972
L3,0402,1,8.2nH RF,C361505
"R1, R2",0402,2,10R,C138066
"R10, R11",0402,2,5.1k,C105872
"R12, R24, R26, R5, R7",0402,5,1k,C106235
R13,0402,1,287R,C375493
R14,0402,1,115R,C295872
R15,0402,1,750R,C137936
"R16, R17, R21, R22",0402,4,2.2k,C114762
"R18, R19",0402,2,27.4R 1%,C284479
"R20, R27, R31, R32, R8, R9",0402,6,10k,C60490
"R23, R25",0402,2,20R,C138031
"R28, R29, R30, R4, R6",0402,5,0R,C60485
R3,0402,1,6.8k,C93940
"SW1, SW2",SOT-363_SC-70-6,2,SN74LVC1G3157,C38663
"SW3, SW4",SW-SMD_L3.9-W3.0-P4.45,2,SW_Push,C455280
"TP1, TP10, TP11, TP2, TP3, TP4, TP5, TP6, TP7, TP8, TP9",TestPoint_Pad_D1.0mm,11,TestPoint,
U1,VSSOP-8_3.0x3.0mm_P0.65mm,1,TLV3542,C2876465
U10,ESP32-PICO-MINI-02U,1,ESP32-PICO-MINI-02U	,C3013939
U2,DFN-8-1EP_2x2mm_P0.5mm_EP0.9x1.5mm,1,BLB01,
U3,MSOP-8_3x3mm_P0.65mm,1,AD8313xRM,C481897
U4,SOT-363_SC-70-6,1,MCP4017-104E 100k,C510890
U5,SOT-223-3_TabPin2,1,AMS1117-3.3,C917183
U6,SOT-353_SC-70-5,1,MCP6566,C623508
U7,TSSOP-8_4.4x3mm_P0.65mm,1,M24C02-RDW,C152731
U8,SOIC-8_5.23x5.23mm_P1.27mm,1,W25Q128JVS,C97521
U9,QFN-56-1EP_7x7mm_P0.4mm_EP3.2x3.2mm,1,RP2040,C2040
X1,Filter_SAW-6_3.0x3.0mm,1,TA2003A,
Y1,Crystal_SMD_3225-4Pin_3.2x2.5mm,1,12.000MHz 18pF ±20ppm 80R,C403945

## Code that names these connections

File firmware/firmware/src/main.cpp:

#include <stdio.h>
#include "pico/stdlib.h"
// #include "hardware/gpio.h"
// #include "hardware/pio.h"
// #include "hardware/clocks.h"
// // #include "hardware/dma.h"
// #include "hardware/irq.h"
// #include "blink.pio.h"
// #include "capture.pio.h"
#include "pico/binary_info.h"
#include "hal.hh"
#include "ads_bee.hh"

// #define LED_PIN 25

// // void dma_handler() {
// //     dma_hw->ints0 = 1u << dma_chan; // clear interrupt request
// // }

// PIO preamble_detector_pio = pio0;
// uint preamble_detector_sm = pio_claim_unused_sm(preamble_detector_pio, true);
// uint preamble_detector_offset = pio_add_program(preamble_detector_pio, &preamble_detector_program);

// PIO message_decoder_pio = pio1;
// uint message_decoder_sm = pio_claim_unused_sm(message_decoder_pio, true);
// uint message_decoder_offset = pio_add_program(message_decoder_pio, &message_decoder_program);

// void on_decode_complete() {
//     printf("New message:\r\n");
//     while (!pio_sm_is_rx_fifo_empty(message_decoder_pio, message_decoder_sm)) {
//         printf("\t%08x\r\n", pio_sm_get(message_decoder_pio, message_decoder_sm));
//         // pio_sm_get(message_decoder_pio, message_decoder_sm);
//     }
//     pio_interrupt_clear(preamble_detector_pio, 0);
// }

int main() {
    bi_decl(bi_program_description("ADS-Bee ADSB Receiver"));

    stdio_init_all();

    ADSBee::ADSBeeConfig config;
    // Override default config params here.
    ADSBee ads_bee = ADSBee(config);
    ads_bee.Init();
    
    while(true) {
        // Loop forever.
        ads_bee.Update();
    }


    // /** PREAMBLE DETECTOR PIO **/
    // static const uint pulses_pin = 19; // Reading ADS-B on GPIO22. Will look for DECODE signal on GPIO22-1 = GPIO21.
    // static const uint decode_in_pin = pulses_pin+1;
    // static const uint decode_out_pin = 21; // Use GPIO20 as DECODE signal output, will be wired to GPIO21 as input.

    // static const float kPreambleDetectorFreq = 16e6; // Running at 16MHz (8 clock cycles per half bit).
    // // Calculate the PIO clock divider.
    // float preamble_detector_div = (float)clock_get_hz(clk_sys) / kPreambleDetectorFreq;

    // // Initialize the program using the .pio file helper function
    // preamble_detector_program_init(
    //     preamble_detector_pio, preamble_detector_sm, preamble_detector_offset, pulses_pin,
    //     decode_out_pin, preamble_detector_div
    // );
    

    // // enable the DECODE interrupt on PIO0_IRQ_0
    // uint preamble_detector_decode_irq = PIO0_IRQ_0;
    // pio_set_irq0_source_enabled(preamble_detector_pio, pis_interrupt0, true); // state machine 0 IRQ 0

    // /** MESSAGE DECODER PIO **/
    // float message_decoder_freq = 16e6; // Run at 32 MHz to decode bits at 1Mbps.
    // float message_decoder_div = (float)clock_get_hz(clk_sys) / message_decoder_freq;
    // message_decoder_program_init(
    //     message_decoder_pio, message_decoder_sm, message_decoder_offset,
    //     pulses_pin, message_decoder_div
    // );

    // // // enable the MESSAGE_READY interrupt on PIO1_IRQ_0
    // // uint message_decoder_message_ready_irq = PIO1_IRQ_0;
    // // pio_set_irq0_source_enabled(message_decoder_pio, pis_interrupt0, true); // state machine 1 IRQ 0

    // printf("main.cpp: PIOs initialized.\r\n");

    // gpio_init(LED_PIN);
    // gpio_set_dir(LED_PIN, GPIO_OUT);

    // irq_set_exclusive_handler(preamble_detector_decode_irq, on_decode_complete);
    // irq_set_enabled(preamble_detector_decode_irq, true);

    // // Enable the state machines
    // pio_sm_set_enabled(preamble_detector_pio, preamble_detector_sm, true);
    // pio_sm_set_enabled(message_decoder_pio, message_decoder_sm, true);

    // // Do nothing
    // while (true) {
    //     gpio_put(LED_PIN, 1);
    //     sleep_ms(500);
    //     gpio_put(LED_PIN, 0);
    //     sleep_ms(500);
    //     // printf("%08x\r\n", pio_sm_get_blocking(message_decoder_pio, message_decoder_sm));
    // }
}

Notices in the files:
README.md:
License: GPL-3.0
